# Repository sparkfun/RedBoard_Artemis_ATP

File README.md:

SparkFun RedBoard Artemis ATP
============================

[*SparkFun RedBoard Artemis ATP (DEV-15442)*](https://www.sparkfun.com/products/15442)

The RedBoard Artemis ATP is affectionately called 'All the Pins!' at SparkFun. The Artemis module has 48 GPIO and this board breaks out absolutely every one of them in a familiar Mega like form factor. What's with the silkscreen labels? They're all over the place. We decided to label the pins as they are assigned on the Apollo3 IC itself. This makes finding the pin with the function you desire a lot easier. Have a look at the [full pin map](https://cdn.sparkfun.com/assets/8/2/3/3/c/Apollo3_Pad_Mapping.pdf) from the Apollo3 datasheet. If you really need to test out the 4-bit SPI functionality of the Artemis you're going to need to access pins 4, 22, 23, and 26. Need to try out the differential ADC port 1? Pins 14 and 15. The RedBoard Artemis ATP will allow you to flex the impressive capabilities of the Artemis module.

The RedBoard Artemis ATP has the improved power conditioning and USB to serial that we've refined over the years on our RedBoard line of products. A modern USB-C connector make programming easy. A Qwiic connector makes I<sup>2</sup>C easy. The ATP is fully compatible with SparkFun's Arduino core and can be programmed easily under the Arduino IDE. We've exposed the JTAG connector for more advanced users who prefer to use the power and speed of professional tools. If you need a *lot* of a GPIO with a simple to program, ready to go to market module, the ATP is the fix you need. We've added a digital MEMS microphone for folks wanting to experiment with always-on voice commands with TensorFlow and machine learning. We've even added a convenient jumper to measure current consumption for low power testing.

With 1M flash and 384k RAM you'll have plenty of room for your sketches. The Artemis module runs at 48MHz with a 96MHz turbo mode available and with Bluetooth to boot!

The SparkFun RedBoard Artemis ATP is a powerful platform if you're interesting in testing out the full capabilities of the SparkFun Artemis module. If you're looking for more compact solution, be sure to checkout our Nano and Uno footprints for more hacker friendly products.

Repository Contents
-------------------
* **/Hardware** - Eagle design files (.brd, .sch)

Documentation
-------------------
* **[Hookup Guide for the RedBoard Artemis ATP](https://learn.sparkfun.com/tutorials/hookup-guide-for-the-sparkfun-redboard-artemis-atp)**
* **[Artemis Development with Arduino](https://learn.sparkfun.com/tutorials/artemis-development-with-arduino)**
* **[Ambiq Apollo3 SDK SetUp](https://learn.sparkfun.com/tutorials/using-sparkfun-edge-board-with-ambiq-apollo3-sdk)**
* **[Designing with the SparkFun Artemis](https://learn.sparkfun.com/tutorials/designing-with-the-sparkfun-artemis)**
* **[CH340E USB to serial IC Drivers](https://www.sparkfun.com/ch340)**

License Information
-------------------

This product is _**open source**_! 

Please review the LICENSE.md file for license information. 

If you have any questions or concerns on licensing, please contact techsupport@sparkfun.com.

Please use, reuse, and modify these files as you see fit. Please maintain attribution to SparkFun Electronics and release any derivative under the same license.

Distributed as-is; no warranty is given.

- Your friends at SparkFun.

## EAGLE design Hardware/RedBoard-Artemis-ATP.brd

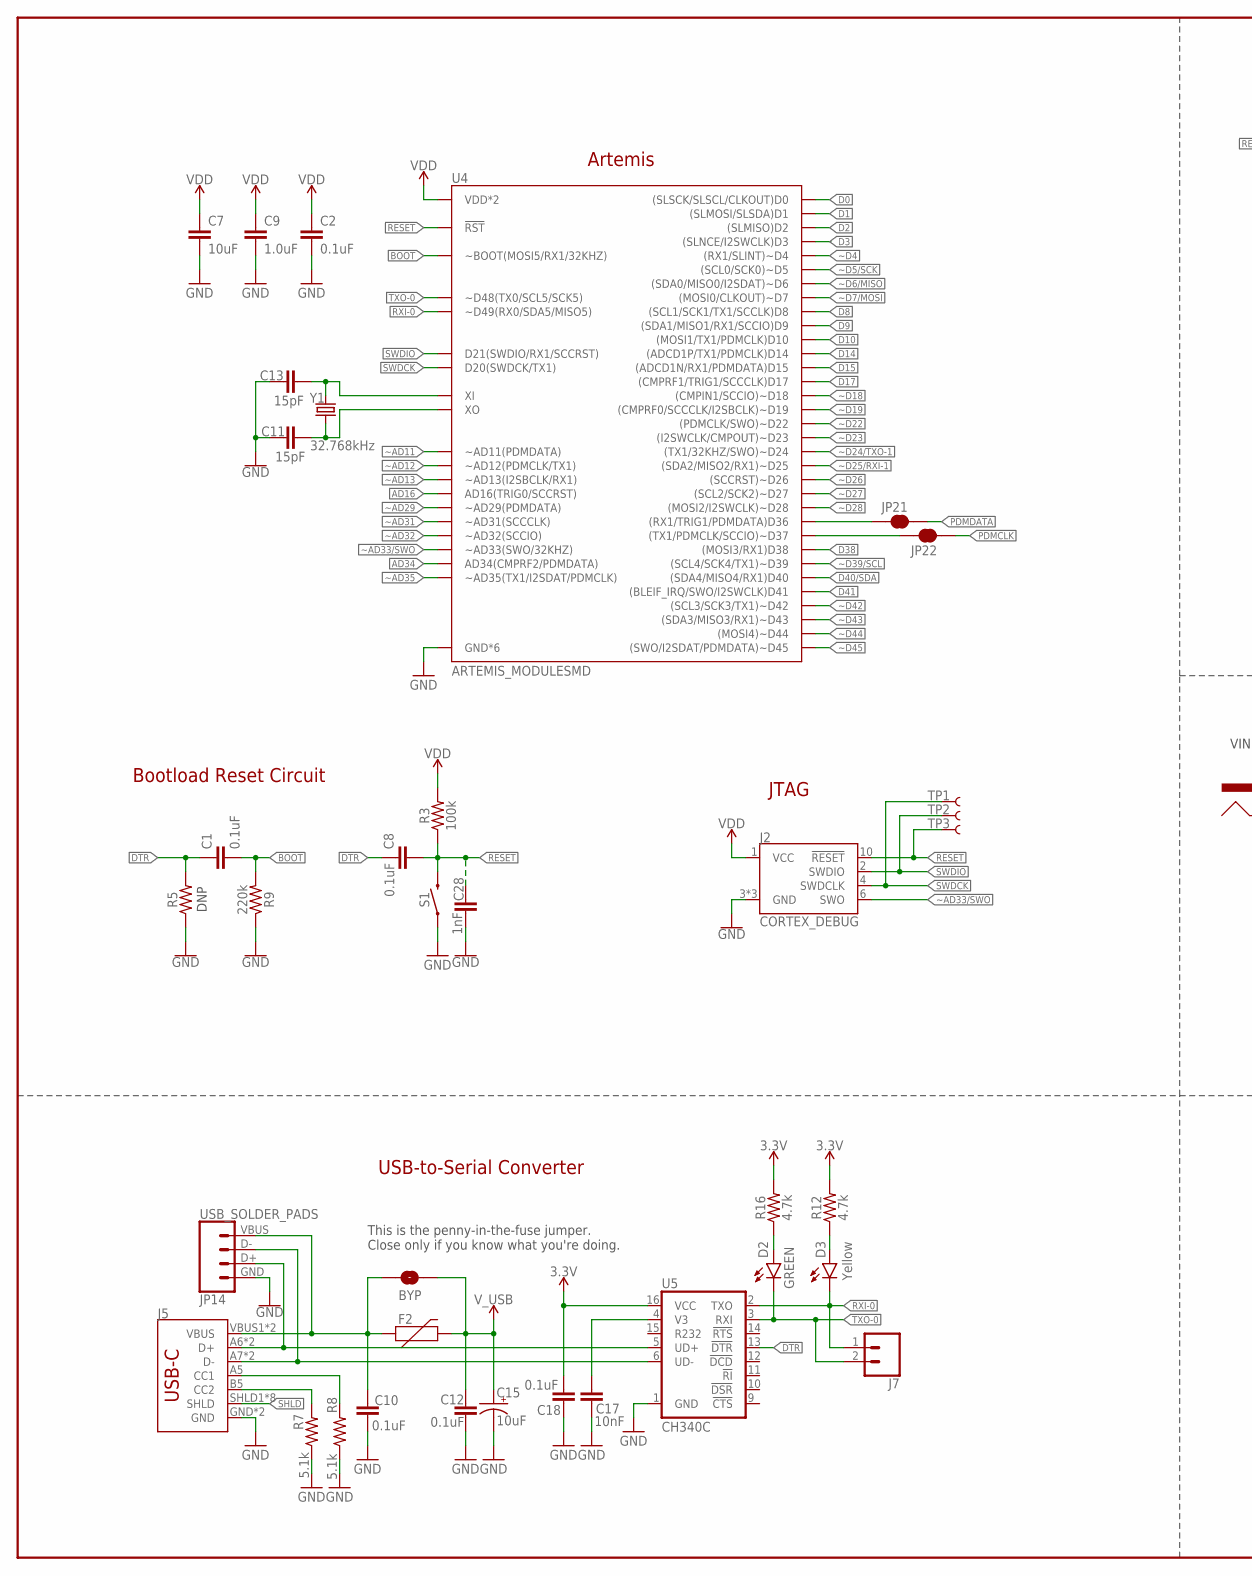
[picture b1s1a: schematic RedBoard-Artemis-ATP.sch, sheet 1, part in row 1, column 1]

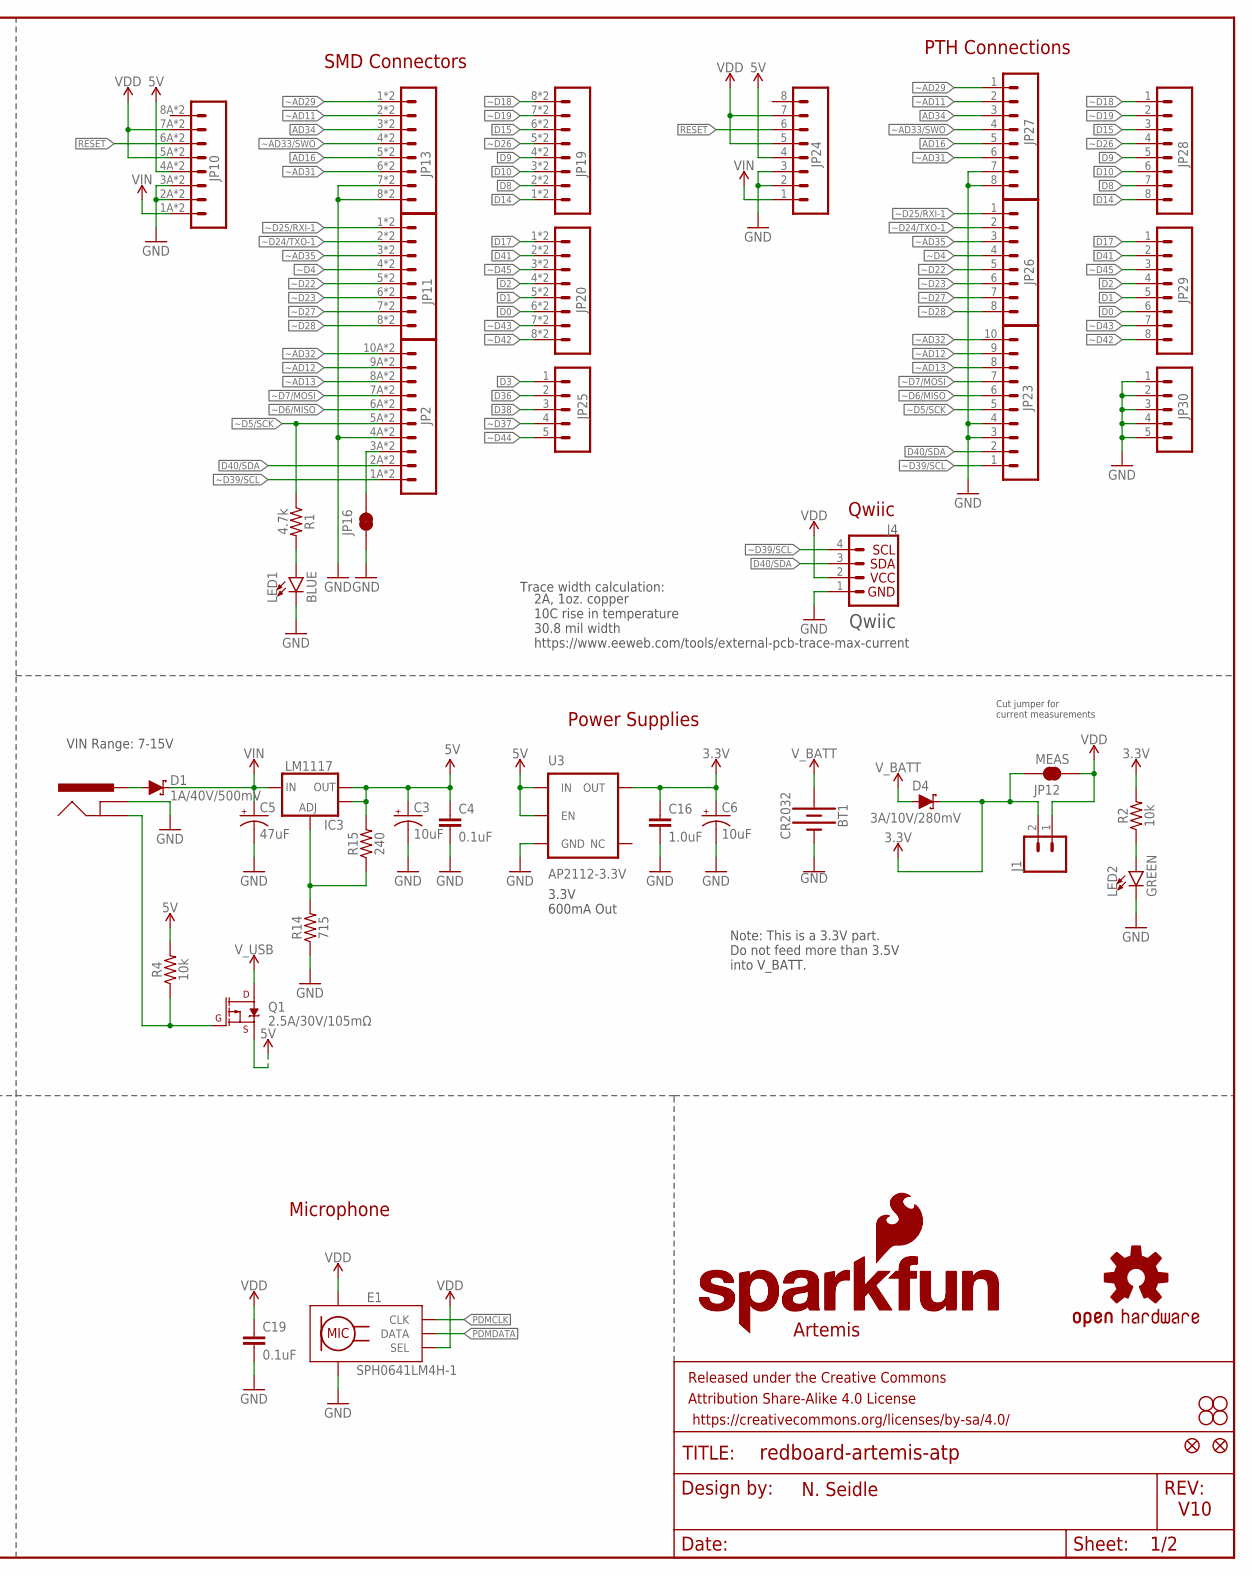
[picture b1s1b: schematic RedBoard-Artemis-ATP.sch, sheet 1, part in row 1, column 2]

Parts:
BT1: CR2032; BATTCON_20MM_4LEGS_OVERPASTE
BYP: BYP; SMT-JUMPER_2_NO_SILK
C1, C2, C4, C8, C10, C12, C18, C19: 0.1uF; 0603
C3, C6, C15: 10uF; EIA3216
C5: 47uF; PANASONIC_D
C7: 10uF; 0603
C9, C16: 1.0uF; 0603
C11, C13: 15pF; 0603
C17: 10nF; 0603
C28: 1nF; 0603
D1: 1A/40V/500mV; SMA-DIODE
D2: GREEN; LED-1206
D3: Yellow; LED-1206
D4: 3A/10V/280mV; SOD-323
E1: SPH0641LM4H-1; SPH0641LM4H-1_MICROPHONE
F2: 6V/2A; 1210
FRAME3: FRAME-LEDGER; CREATIVE_COMMONS
IC3: LM1117; SOT223-ALT1
J1, J7: CONN_021X02_NO_SILK; 1X02_NO_SILK
J2: CORTEX_DEBUG; 2X5-SMD-1.27MM
J3: POWER_JACKTOE; POWER_JACK_SMD_OVERPASTE_TOE
J4: QWIIC_CONNECTORJS-1MM; JST04_1MM_RA
J5: USB-C; USB-C-16P
JP1: SFE_LOGO_NAME.1_INCH; SFE_LOGO_NAME_.1
JP2: CONN_10SMD_COMBO-FEMALE; 1X10_SMD_COMBINED
JP3, JP4, JP5, JP6: STAND-OFF
JP7: SFE_LOGO_FLAME.1_INCH; SFE_LOGO_FLAME_.1
JP8, JP9: FIDUCIAL1X2; FIDUCIAL-1X2
JP10: M08SMD-COMBO; 1X08_SMD_COMBINED@1
JP11, JP13, JP19, JP20: CONN_08SMD-COMBO-FEMALE_NC; 1X08_SMD_COMBINED_NC
JP12: MEAS; SMT-JUMPER_2_NC_TRACE_SILK
JP14: USB_SOLDER_PADS; USB-SOLDER-PADS
JP16, JP21, JP22: JUMPER-SMT_2_NC_TRACE_SILK; SMT-JUMPER_2_NC_TRACE_SILK
JP23: M10NO_SILK; 1X10_NO_SILK@1
JP24: M08NO_SILK; 1X08_NO_SILK@1
JP25, JP30: CONN_05NO_SILK; 1X05_NO_SILK
JP26, JP27, JP28, JP29: CONN_08NO_SILK_FEMALE_PTH; 1X08_NO_SILK
LED1: BLUE; LED-1206
LED2: GREEN; LED-1206
LOGO1: SFE_LOGO_NAME_FLAME.1_INCH; SFE_LOGO_NAME_FLAME_.1
Q1: 2.5A/30V/105mΩ; SOT23-3
R1, R12, R16: 4.7k; 0603
R2, R4: 10k; 0603
R3: 100k; 0603
R5: 0603
R7, R8: 5.1k; 0603
R9: 220k; 0603
R14: 715; 0603
R15: 240; 0603
S1: MOMENTARY-SWITCH-SPST-SMD-5.2-TALL-REDUNDANT; TACTILE_SWITCH_SMD_5.2MM
TP1, TP2, TP3: TEST-POINT3X5; PAD.03X.05
U3: AP2112-3.3V; SOT23-5
U4: ARTEMIS_MODULESMD; ARTEMIS_FP
U5: CH340C; SO016
U$16: OSHW-LOGOS; OSHW-LOGO-S
Y1: 32.768kHz; CRYSTAL-SMD-3.2X1.5MM

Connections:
3.3V: C6.+, C16.1, C18.1, D4.C, J1.2, JP12.1, R2.2, R12.2, R16.2, U3.5 (OUT), U5.16 (VCC)
5V: C3.+, C4.1, IC3.2 (OUT), IC3.4 (OUT), JP10.4A (4), JP10.4B (4), JP24.4, Q1.2 (S), R4.2, R15.2, U3.1 (IN), U3.3 (EN)
!DTR: C1.1, C8.1, R5.2, U5.13 (!DTR)
!RESET: C8.2, C28.1, J2.10 (!RESET), JP10.6A (6), JP10.6B (6), JP24.6, R3.1, S1.3 (2), S1.4 (2), TP3.P$1, U4.~RST (!RST)
AD16: JP13.5, JP13.5@2 (5), JP27.5, U4.AD16 (AD16(TRIG0/SCCRST))
AD34: JP13.3, JP13.3@2 (3), JP27.3, U4.AD34 (AD34(CMPRF2/PDMDATA))
BOOT: C1.2, R9.2, U4.BOOT (~BOOT(MOSI5/RX1/32KHZ))
CC1: J5.A5 (CC1), R8.2
CC2: J5.B5 (CC2), R7.2
D0: JP20.6, JP20.6@2 (6), JP29.6, U4.D0 ((SLSCK/SLSCL/CLKOUT)D0)
D1: JP20.5, JP20.5@2 (5), JP29.5, U4.D1 ((SLMOSI/SLSDA)D1)
D2: JP20.4, JP20.4@2 (4), JP29.4, U4.D2 ((SLMISO)D2)
D3: JP25.1, U4.D3 ((SLNCE/I2SWCLK)D3)
D8: JP19.2, JP19.2@2 (2), JP28.7, U4.D8 ((SCL1/SCK1/TX1/SCCLK)D8)
D9: JP19.4, JP19.4@2 (4), JP28.5, U4.D9 ((SDA1/MISO1/RX1/SCCIO)D9)
D10: JP19.3, JP19.3@2 (3), JP28.6, U4.D10 ((MOSI1/TX1/PDMCLK)D10)
D14: JP19.1, JP19.1@2 (1), JP28.8, U4.D14 ((ADCD1P/TX1/PDMCLK)D14)
D15: JP19.6, JP19.6@2 (6), JP28.3, U4.D15 ((ADCD1N/RX1/PDMDATA)D15)
D17: JP20.1, JP20.1@2 (1), JP29.1, U4.D17 ((CMPRF1/TRIG1/SCCCLK)D17)
D36: JP21.1, JP25.2, U4.D36 ((RX1/TRIG1/PDMDATA)D36)
D38: JP25.3, U4.D38 ((MOSI3/RX1)D38)
D40/SDA: J4.3, JP2.2A (2), JP2.2B (2), JP23.2, U4.D40 ((SDA4/MISO4/RX1)D40)
D41: JP20.2, JP20.2@2 (2), JP29.2, U4.D41 ((BLEIF_IRQ/SWO/I2SWCLK)D41)
D+: J5.A6 (D+), J5.B6 (D+), JP14.D+ (3), U5.5 (UD+)
D-: J5.A7 (D-), J5.B7 (D-), JP14.D- (2), U5.6 (UD-)
GND: BT1.2 (-), C2.1, C3.-, C4.2, C5.-, C6.-, C7.2, C9.2, C10.2, C11.1, C12.2, C13.1, C15.-, C16.2, C17.2, C18.2, C19.2, C28.2, E1.3 (GND), E1.6 (GND), E1.7 (GND), E1.8 (GND), J2.3 (GND), J2.5 (GND), J2.9 (GND), J3.GND (GNDBREAK), J4.1, J5.GND, J5.GND2 (GND), JP2.4A (4), JP2.4B (4), JP10.2A (2), JP10.2B (2), JP10.3A (3), JP10.3B (3), JP13.7, JP13.7@2 (7), JP13.8, JP13.8@2 (8), JP14.GND (4), JP16.1, JP23.3, JP23.4, JP24.2, JP24.3, JP27.7, JP27.8, JP30.1, JP30.2, JP30.3, JP30.4, JP30.5, LED1.C, LED2.C, R5.1, R7.1, R8.1, R9.1, R14.1, S1.1, S1.2 (1), U3.2 (GND), U4.GND@1 (GND*6), U4.GND@22 (GND*6), U4.GND@38 (GND*6), U4.GND@39 (GND*6), U4.GND@47 (GND*6), U4.GND@59 (GND*6), U5.1 (GND)
INSERT: J3.P$4 (GND), Q1.1 (G), R4.1
unnamed: LED1.A, R1.2
unnamed: LED2.A, R2.1
unnamed: D2.A, R16.1
unnamed: C17.1, U5.4 (V3)
unnamed: C11.2, U4.XO, Y1.P$2 (2)
unnamed: C13.2, U4.XI, Y1.P$1 (1)
unnamed: D3.A, R12.1
unnamed: JP2.3A (3), JP2.3B (3), JP16.2
unnamed: IC3.1 (ADJ), R14.2, R15.1
PDMCLK: E1.4 (CLK), JP22.2
PDMDATA: E1.1 (DATA), JP21.2
PWRIN: D1.A, J3.VIN0 (PWR)
RXI-0: D3.C, J7.1, U4.RXI-0 (~D49(RX0/SDA5/MISO5)), U5.2 (TXO)
SHLD: J5.SHLD1 (SHLD), J5.SHLD2 (SHLD), J5.SHLD3 (SHLD), J5.SHLD4 (SHLD), J5.SHLD5 (SHLD), J5.SHLD6 (SHLD), J5.SHLD7 (SHLD), J5.SHLD8 (SHLD)
SWDCK: J2.4 (SWDCLK), TP1.P$1, U4.SWDCK (D20(SWDCK/TX1))
SWDIO: J2.2 (SWDIO), TP2.P$1, U4.SWDIO (D21(SWDIO/RX1/SCCRST))
TXO-0: D2.C, J7.2, U4.TXO-0 (~D48(TX0/SCL5/SCK5)), U5.3 (RXI)
VDD: C2.2, C7.1, C9.1, C19.1, E1.2 (SEL), E1.5 (VDD), J1.1, J2.1 (VCC), J4.2, JP10.5A (5), JP10.5B (5), JP10.7A (7), JP10.7B (7), JP12.2, JP24.5, JP24.7, R3.2, U4.VDD@36 (VDD*2), U4.VDD@37 (VDD*2)
VIN: C5.+, D1.C, IC3.3 (IN), JP10.1A (1), JP10.1B (1), JP24.1
VUSB: BYP.1, C10.1, F2.1, J5.VBUS1 (VBUS), J5.VBUS2 (VBUS), JP14.VBUS (1)
V_BATT: BT1.1 (+), D4.A
V_USB: BYP.2, C12.1, C15.+, F2.2, Q1.3 (D)
~AD11: JP13.2, JP13.2@2 (2), JP27.2, U4.~AD11 (~AD11(PDMDATA))
~AD12: JP2.9A (9), JP2.9B (9), JP23.9, U4.~AD12 (~AD12(PDMCLK/TX1))
~AD13: JP2.8A (8), JP2.8B (8), JP23.8, U4.~AD13 (~AD13(I2SBCLK/RX1))
~AD29: JP13.1, JP13.1@2 (1), JP27.1, U4.~AD29 (~AD29(PDMDATA))
~AD31: JP13.6, JP13.6@2 (6), JP27.6, U4.~AD31 (~AD31(SCCCLK))
~AD32: JP2.10A (10), JP2.10B (10), JP23.10, U4.~AD32 (~AD32(SCCIO))
~AD33/SWO: J2.6 (SWO), JP13.4, JP13.4@2 (4), JP27.4, U4.~AD33/SWO (~AD33(SWO/32KHZ))
~AD35: JP11.3, JP11.3@2 (3), JP26.3, U4.~AD35 (~AD35(TX1/I2SDAT/PDMCLK))
~D4: JP11.4, JP11.4@2 (4), JP26.4, U4.~D4 ((RX1/SLINT)~D4)
~D5/SCK: JP2.5A (5), JP2.5B (5), JP23.5, R1.1, U4.~D5 ((SCL0/SCK0)~D5)
~D6/MISO: JP2.6A (6), JP2.6B (6), JP23.6, U4.~D6 ((SDA0/MISO0/I2SDAT)~D6)
~D7/MOSI: JP2.7A (7), JP2.7B (7), JP23.7, U4.D7 ((MOSI0/CLKOUT)~D7)
~D18: JP19.8, JP19.8@2 (8), JP28.1, U4.~D18 ((CMPIN1/SCCIO)~D18)
~D19: JP19.7, JP19.7@2 (7), JP28.2, U4.~D19 ((CMPRF0/SCCCLK/I2SBCLK)~D19)
~D22: JP11.5, JP11.5@2 (5), JP26.5, U4.~D22 ((PDMCLK/SWO)~D22)
~D23: JP11.6, JP11.6@2 (6), JP26.6, U4.~D23 ((I2SWCLK/CMPOUT)~D23)
~D24/TXO-1: JP11.2, JP11.2@2 (2), JP26.2, U4.~D24 ((TX1/32KHZ/SWO)~D24)
~D25/RXI-1: JP11.1, JP11.1@2 (1), JP26.1, U4.~D25 ((SDA2/MISO2/RX1)~D25)
~D26: JP19.5, JP19.5@2 (5), JP28.4, U4.~D26 ((SCCRST)~D26)
~D27: JP11.7, JP11.7@2 (7), JP26.7, U4.~D27 ((SCL2/SCK2)~D27)
~D28: JP11.8, JP11.8@2 (8), JP26.8, U4.~D28 ((MOSI2/I2SWCLK)~D28)
~D37: JP22.1, JP25.4, U4.~D37 ((TX1/PDMCLK/SCCIO)~D37)
~D39/SCL: J4.4, JP2.1A (1), JP2.1B (1), JP23.1, U4.~D39 ((SCL4/SCK4/TX1)~D39)
~D42: JP20.8, JP20.8@2 (8), JP29.8, U4.~D42 ((SCL3/SCK3/TX1)~D42)
~D43: JP20.7, JP20.7@2 (7), JP29.7, U4.~D43 ((SDA3/MISO3/RX1)~D43)
~D44: JP25.5, U4.~D44 ((MOSI4)~D44)
~D45: JP20.3, JP20.3@2 (3), JP29.3, U4.~D45 ((SWO/I2SDAT/PDMDATA)~D45)

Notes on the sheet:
Artemis
USB-to-Serial Converter
N. Seidle
V10
This is the penny-in-the-fuse jumper. Close only if you know what you're doing.
VIN Range: 7-15V
3.3V 600mA Out
Cut jumper for current measurements
Power Supplies
Microphone
Note: This is a 3.3V part. Do not feed more than 3.5V into V_BATT.
Qwiic
Trace width calculation:
2A, 1oz. copper 10C rise in temperature 30.8 mil width https://www.eeweb.com/tools/external-pcb-trace-max-current
Bootload Reset Circuit
JTAG
DNP
PTH Connections
SMD Connectors

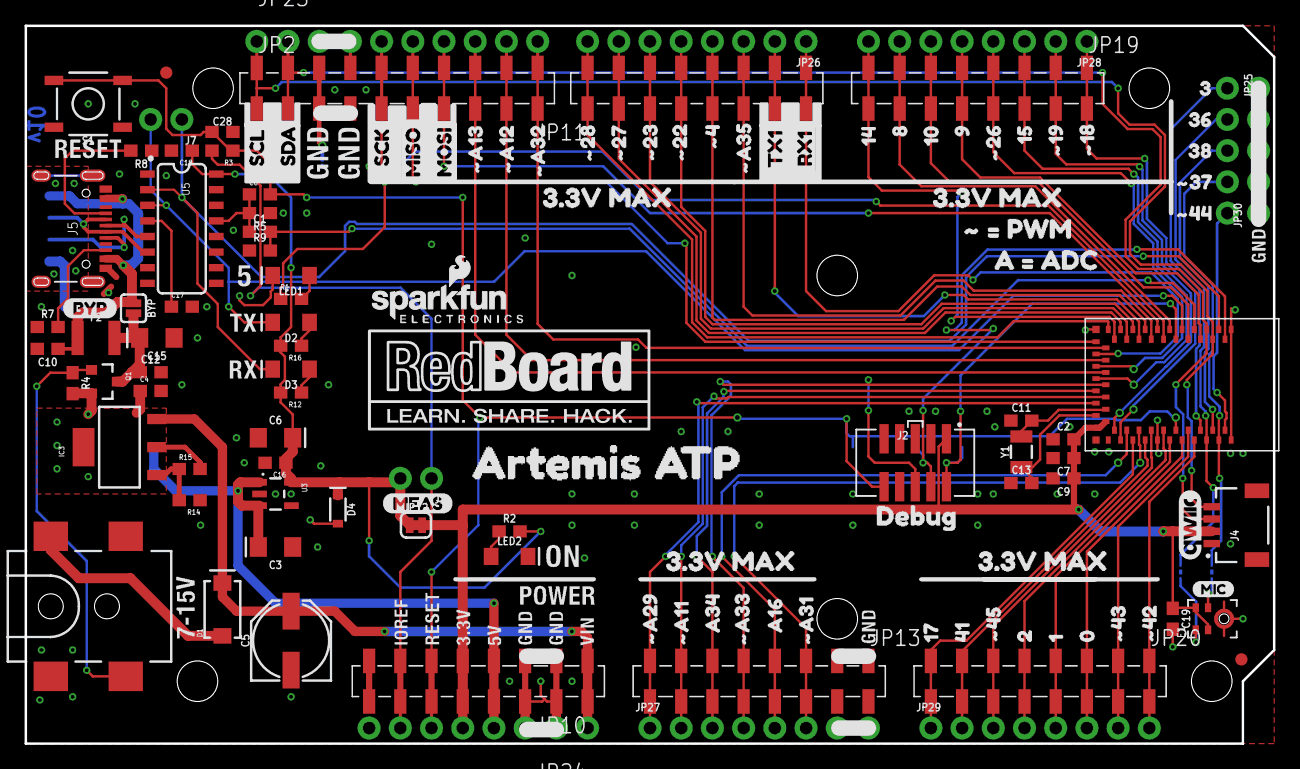
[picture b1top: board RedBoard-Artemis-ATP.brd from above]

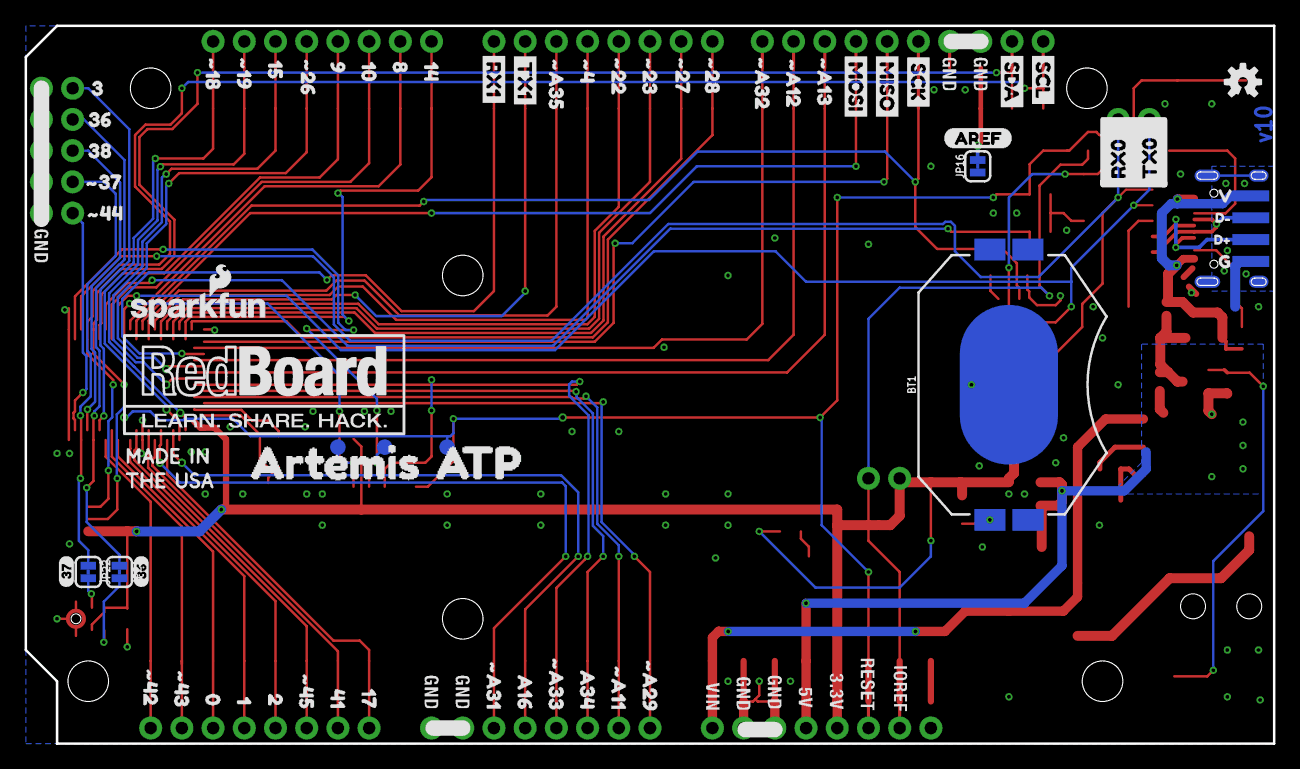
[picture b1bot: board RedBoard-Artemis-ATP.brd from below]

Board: 2 copper layers, 101.6 x 58.4 mm, 201 parts (66 on the bottom side), 76 nets.

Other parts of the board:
FRAME2: FRAME-LETTERNO_PACKAGE; DUMMY
JP17, JP18: STAND-OFF
U$1, U$65, U$67, U$73: 3#3V_MAX2
U$2: D#3
U$3, U$58: 1720
U$4: MADEINUSA#PNG
U$9: QWIIC_COPYRIGHT_SMALL
U$10: D#4
U$11: G1
U$12: V0
U$13, U$112: #A332
U$14, U$15: ARTEMIS0
U$17, U$113: A160
U$18, U$108: SCL1
U$19, U$96: #48
U$20: AREF2
U$21, U$97: #229
U$22, U$107: SDA0
U$23, U$93: #3711
U$24, U$89: #187
U$25, U$98: #2310
U$26, U$100: #2711
U$27, U$99: #2812
U$28, U$61: ATP1
U$29, U$110: #A113
U$30, U$109: #A294
U$31, U$114: #A310
U$32, U$88: #196
U$33, U$95: #A357
U$34, U$102: #A1214
U$35, U$103: #A1315
U$36, U$101: #A3213
U$37, U$86: #264
U$38, U$111: A342
U$39, U$81: #4213
U$40, U$80: #4314
U$41, U$94: #4412
U$42, U$75: #4518
U$43, U$79: 015
U$44, U$90: 38
U$45, U$83: 81
U$46, U$85: 93
U$47, U$105: MISO8
U$48, U$104: MOSI7
U$49: RX01
U$50, U$106: SCK9
U$51, U$84: 102
U$52, U$78: 116
U$53: TX00
U$54, U$82: 140
U$55, U$87: 155
U$56, U$77: 217
U$57, U$91: 369
U$59, U$92: 3810
U$60, U$74: 4119
U$62: MIC0
U$63: 364
U$64: 373
U$66: #_#_PWM7
U$68: BYP0
U$69: A_#_ADC6
U$70: MEAS3
U$71, U$115: RX11
U$72, U$116: TX10
U$76: DEBUG2

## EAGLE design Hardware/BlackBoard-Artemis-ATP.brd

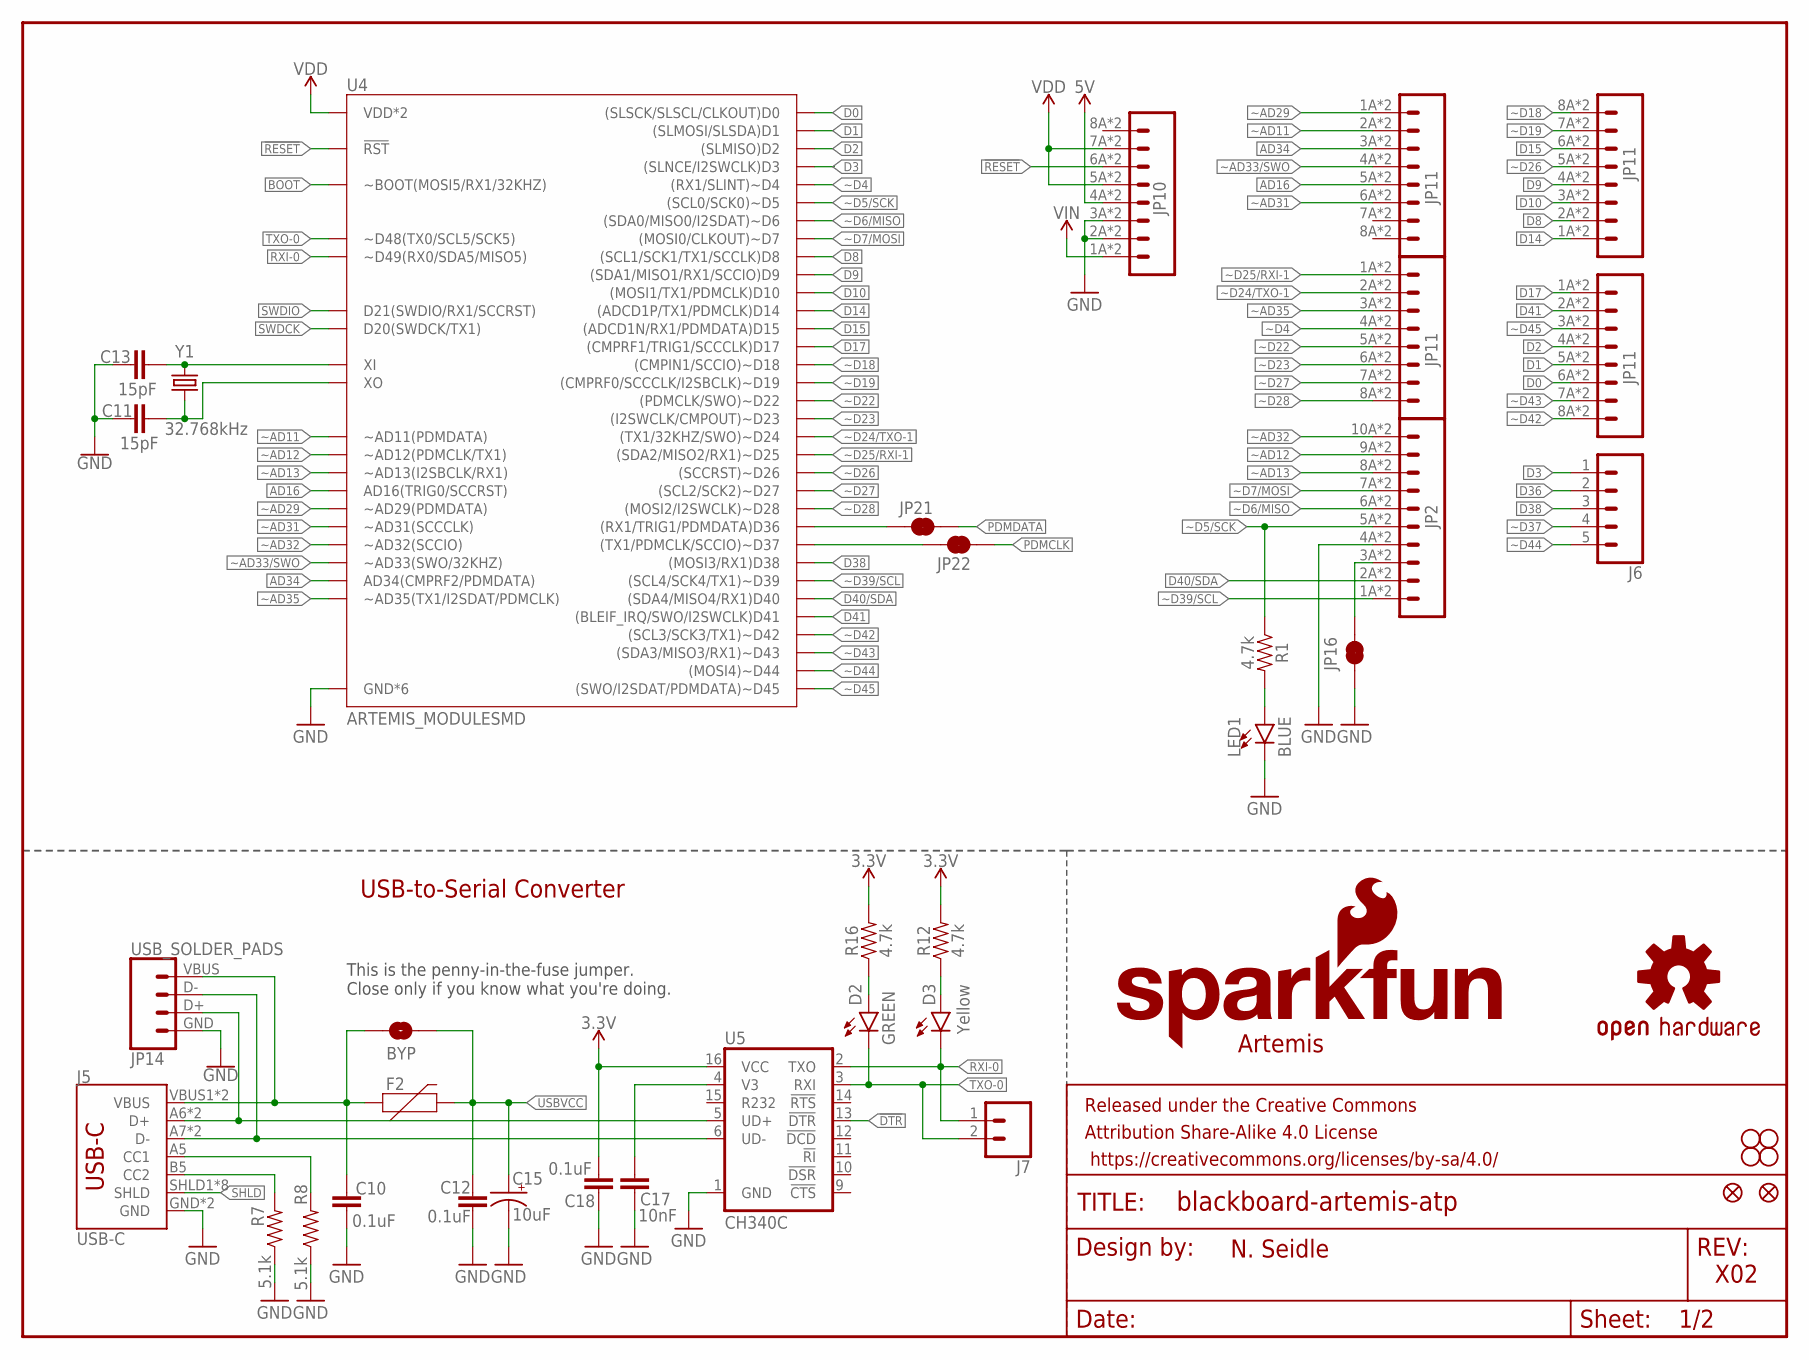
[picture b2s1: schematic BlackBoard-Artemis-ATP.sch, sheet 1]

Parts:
BYP: BYP; SMT-JUMPER_2_NO_SILK
C10, C12, C18: 0.1uF; 0603
C11, C13: 15pF; 0603
C15: 10uF; EIA3216
C17: 10nF; 0603
D2: GREEN; LED-1206
D3: Yellow; LED-1206
F2: 6V/2A; 1210
FRAME1: FRAME-LETTER; CREATIVE_COMMONS
J5: USB-C; USB-C-16P
J6: CONN_05NO_SILK; 1X05_NO_SILK
J7: CONN_021X02_NO_SILK; 1X02_NO_SILK
JP1: SFE_LOGO_NAME.1_INCH; SFE_LOGO_NAME_.1
JP2: M10SMD_COMBO; 1X10_SMD_COMBINED
JP3, JP4, JP5, JP6: STAND-OFF
JP7: SFE_LOGO_FLAME.1_INCH; SFE_LOGO_FLAME_.1
JP8, JP9: FIDUCIAL1X2; FIDUCIAL-1X2
JP10: M08SMD-COMBO; 1X08_SMD_COMBINED
JP11, JP13, JP19, JP20: JP11; 1X08_SMD_COMBINED
JP14: USB_SOLDER_PADS; USB-SOLDER-PADS
JP16, JP21, JP22: JUMPER-SMT_2_NC_TRACE_SILK; SMT-JUMPER_2_NC_TRACE_SILK
LED1: BLUE; LED-1206
R1, R12, R16: 4.7k; 0603
R7, R8: 5.1k; 0603
U4: ARTEMIS_MODULESMD; ARTEMIS_FP
U5: CH340C; SO016
U$16: OSHW-LOGOS; OSHW-LOGO-S
Y1: 32.768kHz; CRYSTAL-SMD-3.2X1.5MM

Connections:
3.3V: C18.1, R12.2, R16.2, U5.16 (VCC); also elsewhere on the board
5V: JP10.4A (4), JP10.4B (4); also elsewhere on the board
!DTR: U5.13 (!DTR); also elsewhere on the board
!RESET: JP10.6A (6), JP10.6B (6), U4.~RST (!RST); also elsewhere on the board
AD16: JP13.5A (5), JP13.5B (5), U4.AD16 (AD16(TRIG0/SCCRST))
AD34: JP13.3A (3), JP13.3B (3), U4.AD34 (AD34(CMPRF2/PDMDATA))
BOOT: U4.BOOT (~BOOT(MOSI5/RX1/32KHZ)); also elsewhere on the board
CC1: J5.A5 (CC1), R8.2
CC2: J5.B5 (CC2), R7.2
D0: JP20.6A (6), JP20.6B (6), U4.D0 ((SLSCK/SLSCL/CLKOUT)D0)
D1: JP20.5A (5), JP20.5B (5), U4.D1 ((SLMOSI/SLSDA)D1)
D2: JP20.4A (4), JP20.4B (4), U4.D2 ((SLMISO)D2)
D3: J6.1, U4.D3 ((SLNCE/I2SWCLK)D3)
D8: JP19.2A (2), JP19.2B (2), U4.D8 ((SCL1/SCK1/TX1/SCCLK)D8)
D9: JP19.4A (4), JP19.4B (4), U4.D9 ((SDA1/MISO1/RX1/SCCIO)D9)
D10: JP19.3A (3), JP19.3B (3), U4.D10 ((MOSI1/TX1/PDMCLK)D10)
D14: JP19.1A (1), JP19.1B (1), U4.D14 ((ADCD1P/TX1/PDMCLK)D14)
D15: JP19.6A (6), JP19.6B (6), U4.D15 ((ADCD1N/RX1/PDMDATA)D15)
D17: JP20.1A (1), JP20.1B (1), U4.D17 ((CMPRF1/TRIG1/SCCCLK)D17)
D36: J6.2, JP21.1, U4.D36 ((RX1/TRIG1/PDMDATA)D36)
D38: J6.3, U4.D38 ((MOSI3/RX1)D38)
D40/SDA: JP2.2A (2), JP2.2B (2), U4.D40 ((SDA4/MISO4/RX1)D40); also elsewhere on the board
D41: JP20.2A (2), JP20.2B (2), U4.D41 ((BLEIF_IRQ/SWO/I2SWCLK)D41)
D+: J5.A6 (D+), J5.B6 (D+), JP14.D+ (3), U5.5 (UD+)
D-: J5.A7 (D-), J5.B7 (D-), JP14.D- (2), U5.6 (UD-)
GND: C10.2, C11.1, C12.2, C13.1, C15.-, C17.2, C18.2, J5.GND, J5.GND2 (GND), JP2.4A (4), JP2.4B (4), JP10.2A (2), JP10.2B (2), JP10.3A (3), JP10.3B (3), JP14.GND (4), JP16.1, LED1.C, R7.1, R8.1, U4.GND@1 (GND*6), U4.GND@22 (GND*6), U4.GND@38 (GND*6), U4.GND@39 (GND*6), U4.GND@47 (GND*6), U4.GND@59 (GND*6), U5.1 (GND); also elsewhere on the board
unnamed: LED1.A, R1.2
unnamed: D2.A, R16.1
unnamed: C17.1, U5.4 (V3)
unnamed: C11.2, U4.XO, Y1.P$2 (2)
unnamed: C13.2, U4.XI, Y1.P$1 (1)
unnamed: D3.A, R12.1
unnamed: JP2.3A (3), JP2.3B (3), JP16.2
PDMCLK: JP22.2; also elsewhere on the board
PDMDATA: JP21.2; also elsewhere on the board
RXI-0: D3.C, J7.1, U4.RXI-0 (~D49(RX0/SDA5/MISO5)), U5.2 (TXO)
SHLD: J5.SHLD1 (SHLD), J5.SHLD2 (SHLD), J5.SHLD3 (SHLD), J5.SHLD4 (SHLD), J5.SHLD5 (SHLD), J5.SHLD6 (SHLD), J5.SHLD7 (SHLD), J5.SHLD8 (SHLD)
SWDCK: U4.SWDCK (D20(SWDCK/TX1)); also elsewhere on the board
SWDIO: U4.SWDIO (D21(SWDIO/RX1/SCCRST)); also elsewhere on the board
TXO-0: D2.C, J7.2, U4.TXO-0 (~D48(TX0/SCL5/SCK5)), U5.3 (RXI)
USBVCC: BYP.2, C12.1, C15.+, F2.2; also elsewhere on the board
VDD: JP10.5A (5), JP10.5B (5), JP10.7A (7), JP10.7B (7), U4.VDD@36 (VDD*2), U4.VDD@37 (VDD*2); also elsewhere on the board
VIN: JP10.1A (1), JP10.1B (1); also elsewhere on the board
VUSB: BYP.1, C10.1, F2.1, J5.VBUS1 (VBUS), J5.VBUS2 (VBUS), JP14.VBUS (1)
~AD11: JP13.2A (2), JP13.2B (2), U4.~AD11 (~AD11(PDMDATA))
~AD12: JP2.9A (9), JP2.9B (9), U4.~AD12 (~AD12(PDMCLK/TX1))
~AD13: JP2.8A (8), JP2.8B (8), U4.~AD13 (~AD13(I2SBCLK/RX1))
~AD29: JP13.1A (1), JP13.1B (1), U4.~AD29 (~AD29(PDMDATA))
~AD31: JP13.6A (6), JP13.6B (6), U4.~AD31 (~AD31(SCCCLK))
~AD32: JP2.10A (10), JP2.10B (10), U4.~AD32 (~AD32(SCCIO))
~AD33/SWO: JP13.4A (4), JP13.4B (4), U4.~AD33/SWO (~AD33(SWO/32KHZ)); also elsewhere on the board
~AD35: JP11.3A (3), JP11.3B (3), U4.~AD35 (~AD35(TX1/I2SDAT/PDMCLK))
~D4: JP11.4A (4), JP11.4B (4), U4.~D4 ((RX1/SLINT)~D4)
~D5/SCK: JP2.5A (5), JP2.5B (5), R1.1, U4.~D5 ((SCL0/SCK0)~D5)
~D6/MISO: JP2.6A (6), JP2.6B (6), U4.~D6 ((SDA0/MISO0/I2SDAT)~D6)
~D7/MOSI: JP2.7A (7), JP2.7B (7), U4.D7 ((MOSI0/CLKOUT)~D7)
~D18: JP19.8A (8), JP19.8B (8), U4.~D18 ((CMPIN1/SCCIO)~D18)
~D19: JP19.7A (7), JP19.7B (7), U4.~D19 ((CMPRF0/SCCCLK/I2SBCLK)~D19)
~D22: JP11.5A (5), JP11.5B (5), U4.~D22 ((PDMCLK/SWO)~D22)
~D23: JP11.6A (6), JP11.6B (6), U4.~D23 ((I2SWCLK/CMPOUT)~D23)
~D24/TXO-1: JP11.2A (2), JP11.2B (2), U4.~D24 ((TX1/32KHZ/SWO)~D24)
~D25/RXI-1: JP11.1A (1), JP11.1B (1), U4.~D25 ((SDA2/MISO2/RX1)~D25)
~D26: JP19.5A (5), JP19.5B (5), U4.~D26 ((SCCRST)~D26)
~D27: JP11.7A (7), JP11.7B (7), U4.~D27 ((SCL2/SCK2)~D27)
~D28: JP11.8A (8), JP11.8B (8), U4.~D28 ((MOSI2/I2SWCLK)~D28)
~D37: J6.4, JP22.1, U4.~D37 ((TX1/PDMCLK/SCCIO)~D37)
~D39/SCL: JP2.1A (1), JP2.1B (1), U4.~D39 ((SCL4/SCK4/TX1)~D39); also elsewhere on the board
~D42: JP20.8A (8), JP20.8B (8), U4.~D42 ((SCL3/SCK3/TX1)~D42)
~D43: JP20.7A (7), JP20.7B (7), U4.~D43 ((SDA3/MISO3/RX1)~D43)
~D44: J6.5, U4.~D44 ((MOSI4)~D44)
~D45: JP20.3A (3), JP20.3B (3), U4.~D45 ((SWO/I2SDAT/PDMDATA)~D45)

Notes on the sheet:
Artemis
USB-to-Serial Converter
N. Seidle
X02
This is the penny-in-the-fuse jumper. Close only if you know what you're doing.

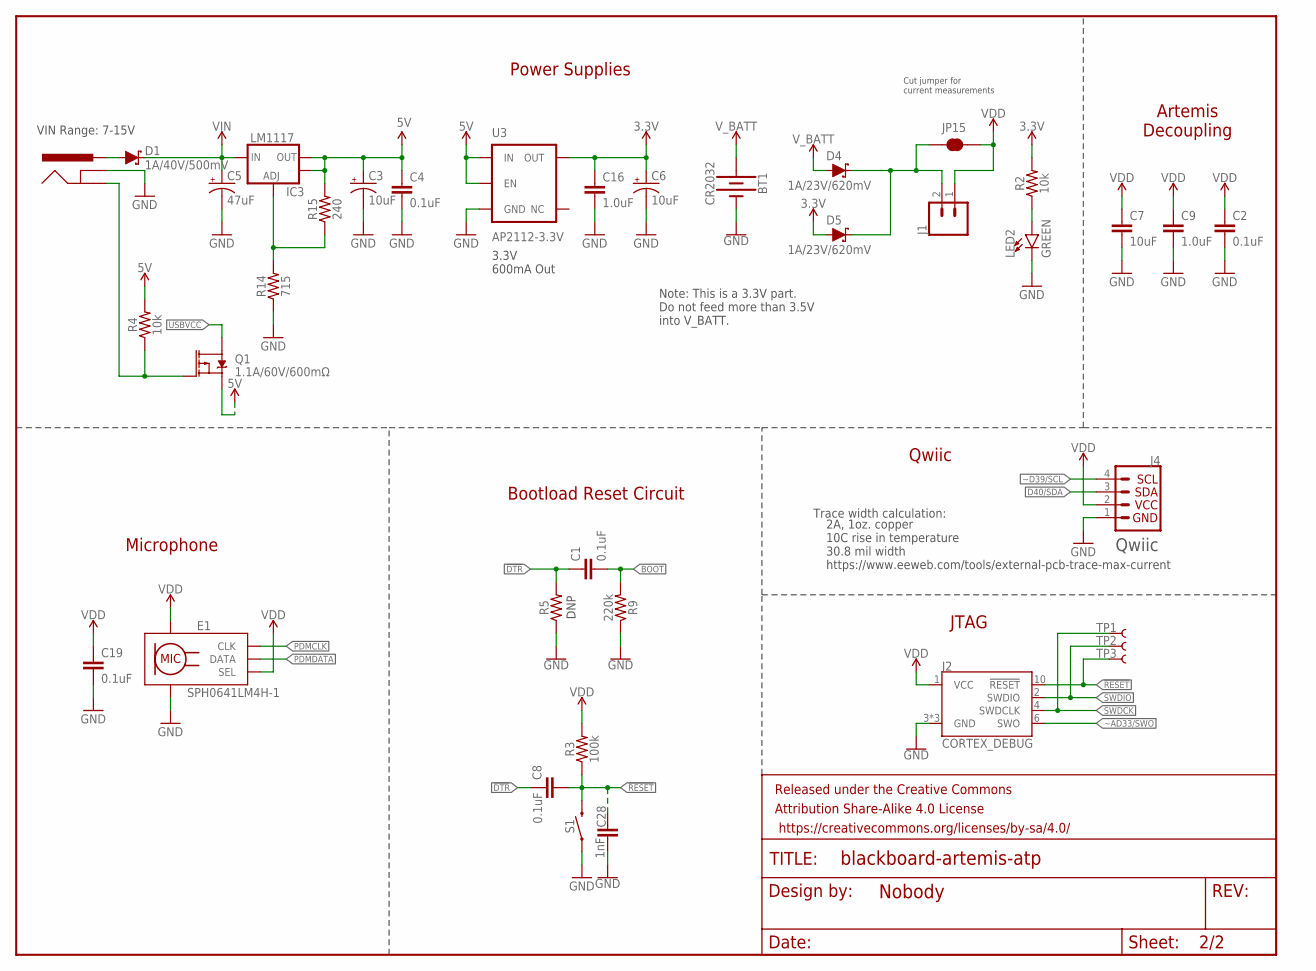
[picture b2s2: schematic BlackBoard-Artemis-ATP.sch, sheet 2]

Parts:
BT1: CR2032; BATTCON_20MM_4LEGS_OVERPASTE
C1, C2, C4, C8, C19: 0.1uF; 0603
C3, C6: 10uF; EIA3216
C5: 47uF; PANASONIC_D
C7: 10uF; 0603
C9, C16: 1.0uF; 0603
C28: 1nF; 0603
D1: 1A/40V/500mV; SMA-DIODE
D4, D5: 1A/23V/620mV; SOD-323
E1: SPH0641LM4H-1; SPH0641LM4H-1_MICROPHONE
FRAME2: FRAME-LETTERNO_PACKAGE; DUMMY
IC3: LM1117; SOT223-ALT1
J1: CONN_021X02_NO_SILK; 1X02_NO_SILK
J2: CORTEX_DEBUG; 2X5-PTH-1.27MM-NO_SILK
J3: POWER_JACKTOE; POWER_JACK_SMD_OVERPASTE_TOE
J4: QWIIC_CONNECTORJS-1MM; JST04_1MM_RA
JP15: JUMPER-SMT_2_NC_TRACE_SILK; SMT-JUMPER_2_NC_TRACE_SILK
LED2: GREEN; LED-1206
Q1: 1.1A/60V/600mΩ; SOT23-3
R2, R4: 10k; 0603
R3: 100k; 0603
R5: 0603
R9: 220k; 0603
R14: 715; 0603
R15: 240; 0603
S1: MOMENTARY-SWITCH-SPST-SMD-5.2-TALL-REDUNDANT; TACTILE_SWITCH_SMD_5.2MM
TP1, TP2, TP3: TEST-POINT3X5; PAD.03X.05
U3: AP2112-3.3V; SOT23-5

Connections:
3.3V: C6.+, C16.1, D5.A, R2.2, U3.5 (OUT); also elsewhere on the board
5V: C3.+, C4.1, IC3.2 (OUT), IC3.4 (OUT), Q1.2 (S), R4.2, R15.2, U3.1 (IN), U3.3 (EN); also elsewhere on the board
!DTR: C1.1, C8.1, R5.2; also elsewhere on the board
!RESET: C8.2, C28.1, J2.10 (!RESET), R3.1, S1.3 (2), S1.4 (2), TP3.P$1; also elsewhere on the board
BOOT: C1.2, R9.2; also elsewhere on the board
D40/SDA: J4.3; also elsewhere on the board
GND: BT1.2 (-), C2.1, C3.-, C4.2, C5.-, C6.-, C7.2, C9.2, C16.2, C19.2, C28.2, E1.3 (GND), E1.6 (GND), E1.7 (GND), E1.8 (GND), J2.3 (GND), J2.5 (GND), J2.9 (GND), J3.GND (GNDBREAK), J4.1, LED2.C, R5.1, R9.1, R14.1, S1.1, S1.2 (1), U3.2 (GND); also elsewhere on the board
INSERT: J3.P$4 (GND), Q1.1 (G), R4.1
unnamed: LED2.A, R2.1
unnamed: D4.C, D5.C, J1.2, JP15.1
unnamed: IC3.1 (ADJ), R14.2, R15.1
PDMCLK: E1.4 (CLK); also elsewhere on the board
PDMDATA: E1.1 (DATA); also elsewhere on the board
PWRIN: D1.A, J3.VIN0 (PWR)
SWDCK: J2.4 (SWDCLK), TP1.P$1; also elsewhere on the board
SWDIO: J2.2 (SWDIO), TP2.P$1; also elsewhere on the board
USBVCC: Q1.3 (D); also elsewhere on the board
VDD: C2.2, C7.1, C9.1, C19.1, E1.2 (SEL), E1.5 (VDD), J1.1, J2.1 (VCC), J4.2, JP15.2, R3.2; also elsewhere on the board
VIN: C5.+, D1.C, IC3.3 (IN); also elsewhere on the board
V_BATT: BT1.1 (+), D4.A
~AD33/SWO: J2.6 (SWO); also elsewhere on the board
~D39/SCL: J4.4; also elsewhere on the board

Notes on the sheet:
VIN Range: 7-15V
3.3V 600mA Out
Cut jumper for current measurements
Power Supplies
Microphone
Note: This is a 3.3V part. Do not feed more than 3.5V into V_BATT.
Qwiic
Trace width calculation:
2A, 1oz. copper 10C rise in temperature 30.8 mil width https://www.eeweb.com/tools/external-pcb-trace-max-current
Bootload Reset Circuit
JTAG
Artemis Decoupling
DNP

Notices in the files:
parts and their libraries:
SparkFun-Aesthetics: Licensing: CC v3.0 Share-Alike You are welcome to use this library for commercial purposes.
SparkFun-Aesthetics: Released under the Creative Commons Attribution Share-Alike 4.0 License
SparkFun-Aesthetics: https://creativecommons.org/licenses/by-sa/4.0
